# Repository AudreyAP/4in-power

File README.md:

# Power Module Repository

---

<div align="center">
  <div>

    <p><em>3D Render</em></p>
  </div>
  <br>

  <div>
    <br>
    <p><em>Schematic</em></p>
  </div>
  <br>
  
  <div>
    
    <br>
    <em>Footprint</em>
  </div>
</div>

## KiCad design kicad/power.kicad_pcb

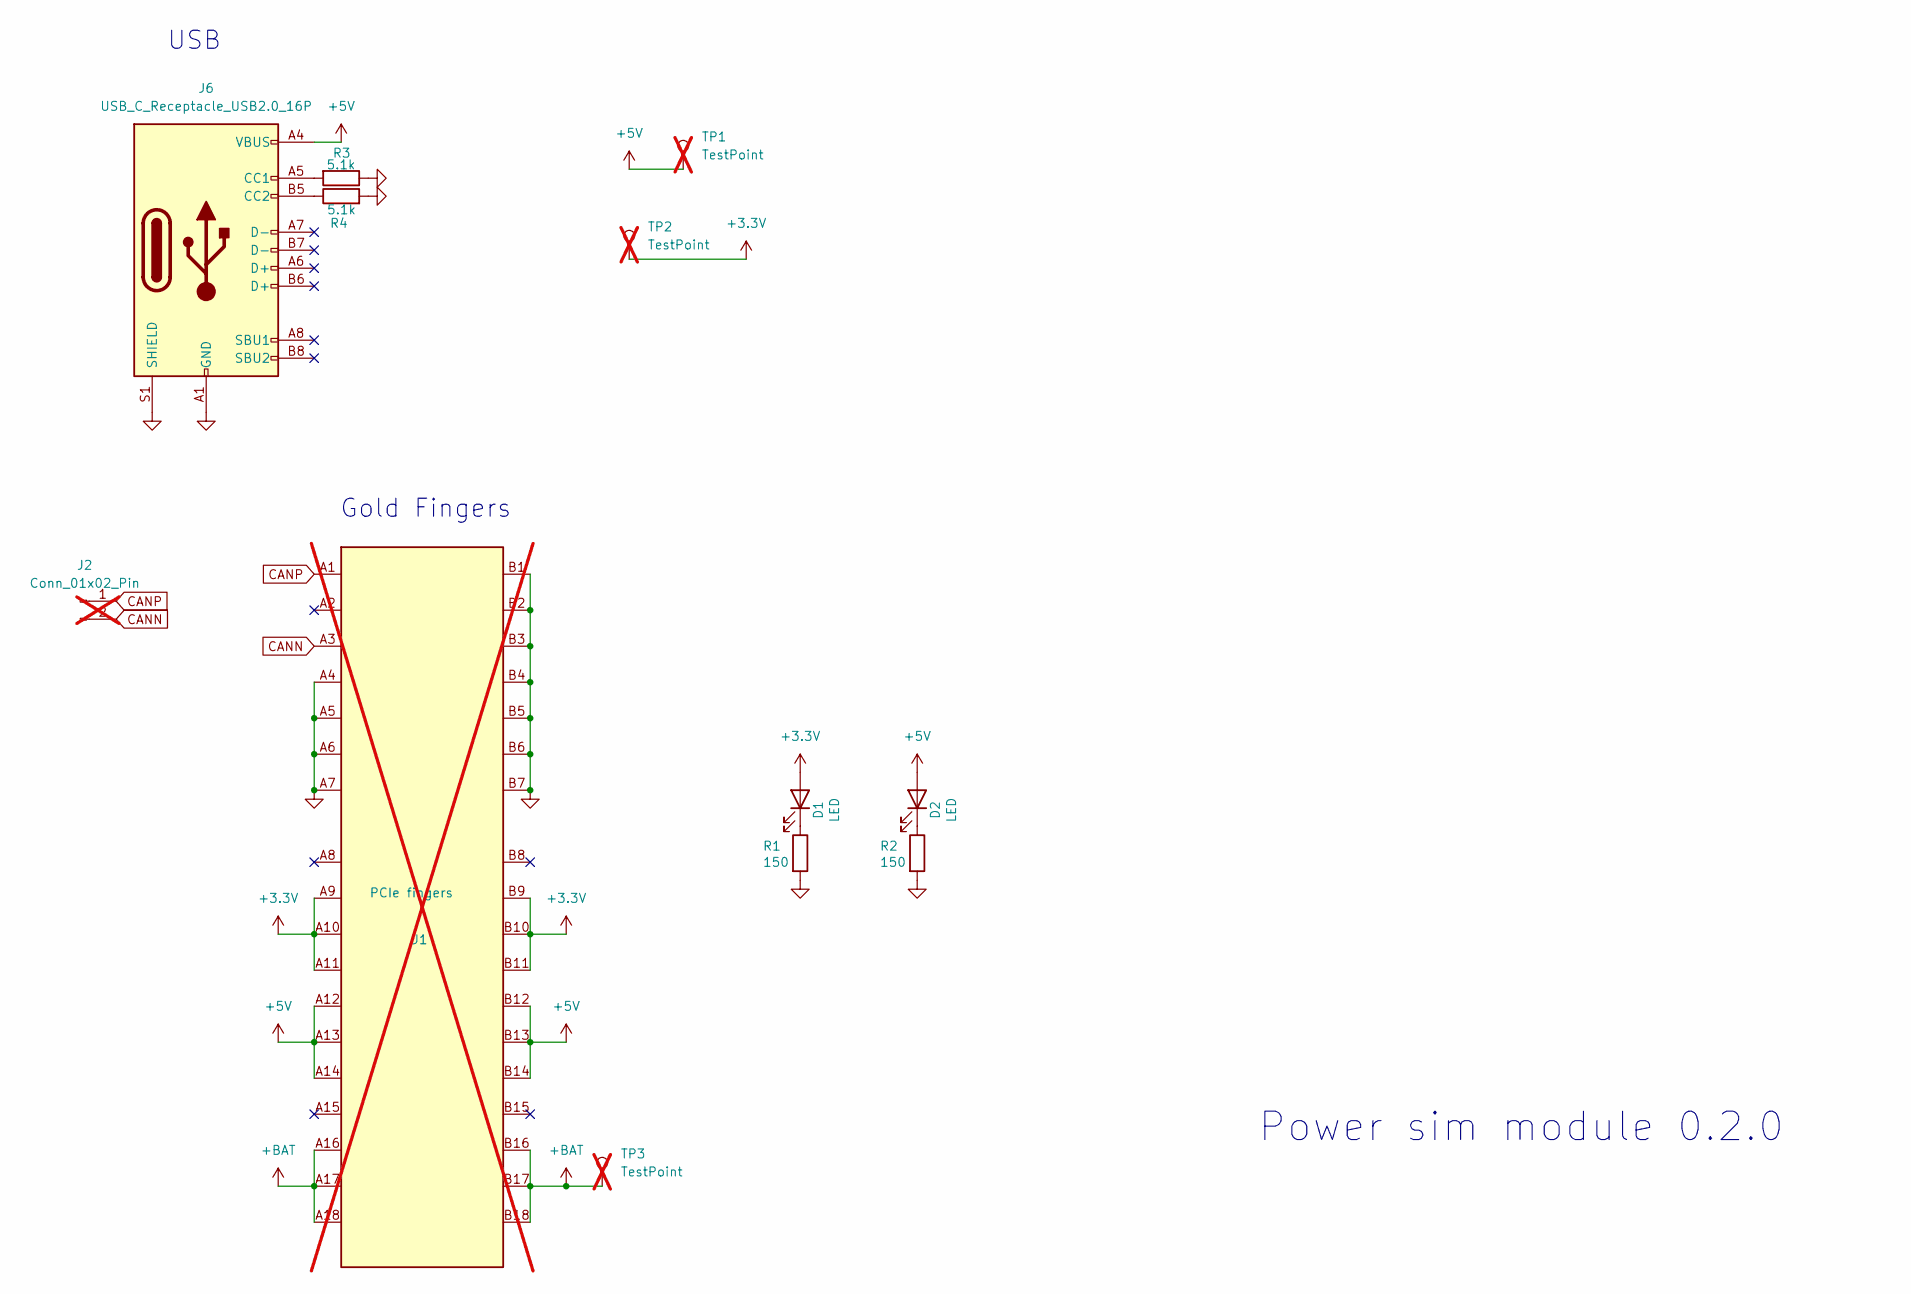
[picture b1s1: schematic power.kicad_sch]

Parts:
D1, D2: LED; LED_0603_1608Metric; LCSC Part # C2286
J1: Bus_PCI_Express_x1; BUS_PCIexpress_x1; LCSC Part # n/a; not fitted
J2: Conn_01x02_Pin; PinHeader_1x02_P2.54mm_Vertical; not fitted
J6: USB_C_Receptacle_USB2.0_16P; USB_C_Receptacle_Palconn_UTC16-G; LCSC Part # C2765186
R1, R2: 150; R_0603_1608Metric; LCSC Part # C22808
R3, R4: 5.1k; R_0402_1005Metric; LCSC Part # C25905
TP1, TP2, TP3: TestPoint; PinHeader_1x01_P2.54mm_Vertical; not fitted

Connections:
+3.3V: D1.2 (A), J1.A9 (+3.3V), J1.A10 (+3.3V), J1.A11 (~PERST), J1.B9 (JTAG1), J1.B10 (3.3Vaux), J1.B11 (~WAKE), TP2.1
+5V: D2.2 (A), J1.A12 (GND), J1.A13 (REFCLK+), J1.A14 (REFCLK-), J1.B12 (RSVD), J1.B13 (GND), J1.B14 (PETp0), J6.A4 (VBUS), J6.A9 (VBUS), J6.B4 (VBUS), J6.B9 (VBUS), TP1.1
+BAT: J1.A16 (PERp0), J1.A17 (PERn0), J1.A18 (GND), J1.B16 (GND), J1.B17 (~PRSNT2), J1.B18 (GND), TP3.1
CANN: J1.A3 (+12V), J2.2
CANP: J1.A1 (~PRSNT1), J2.1
GND: J1.A4 (GND), J1.A5 (JTAG2), J1.A6 (JTAG3), J1.A7 (JTAG4), J1.B1 (+12V), J1.B2 (+12V), J1.B3 (+12V), J1.B4 (GND), J1.B5 (SMCLK), J1.B6 (SMDAT), J1.B7 (GND), J6.A1 (GND), J6.A12 (GND), J6.B1 (GND), J6.B12 (GND), J6.S1 (SHIELD), R1.2, R2.2, R3.1, R4.2
unnamed: D1.1 (K), R1.1
unnamed: D2.1 (K), R2.1
unnamed: J6.A5 (CC1), R3.2
unnamed: J6.B5 (CC2), R4.1

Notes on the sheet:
USB
Power sim module 0.2.0
Gold Fingers

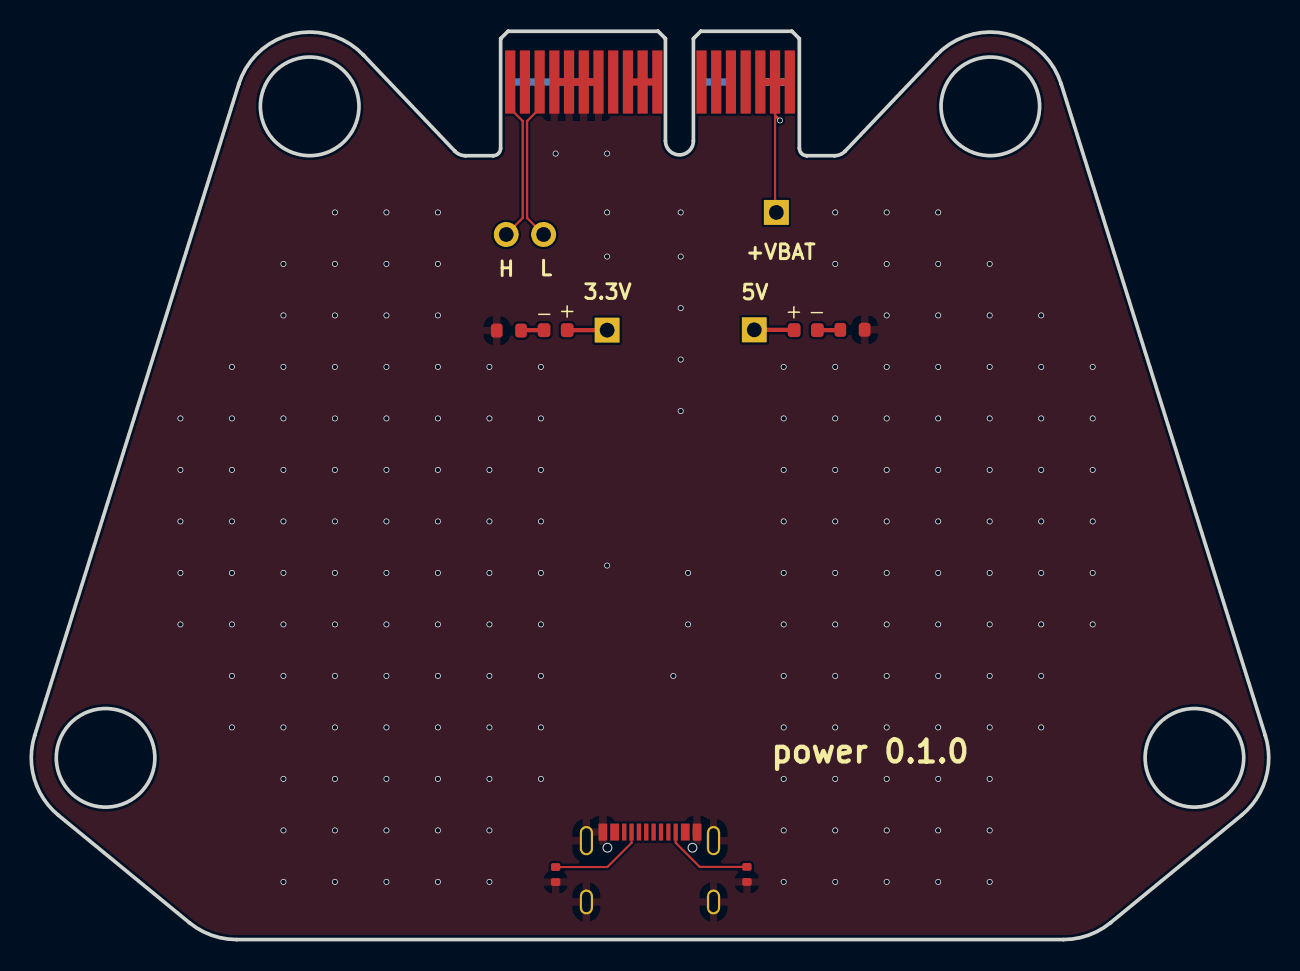
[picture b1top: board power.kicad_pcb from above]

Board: 2 copper layers, 84.1 x 61.7 mm, 12 parts (1 on the bottom side), 10 nets.

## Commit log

2025-02-04 chore: Clone and adapt PowerSim for new project Power
    Cloned the PowerSim project as a foundation for Power. Renamed and restructured components to fit the new project's goals while keeping the core functionality intact. This allows Power to operate dif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
2025-02-04 ci: Add GitHub workflows
2025-02-04 feat: Add components for battery management, charging, and protection
2025-02-04 feat: Update 2S protection
2025-02-04 feat: Update 8.4V to 5V DC-DC converter
2025-02-05 feat: Update 8.4V to 3.3V DC-DC converter
2025-02-05 feat: add charging
2025-02-05 Update images
2025-03-08 rename step to power.step
2025-03-13 add battery CAD to power submodule
2025-03-13 create battery 4 cell assembly
2025-03-17 update battery
2025-03-18 update power cad
2025-03-25 remove temporary SolidWorks files for 18650 part and battery pack assembly
2025-05-06 remove *.kicad_prl and add to gitignore
